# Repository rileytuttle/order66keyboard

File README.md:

# order66keyboard

BUILDING THIS KEYBOARD

checkout this repo
```
git clone git@github.com:rileytuttle/order66keyboard.git
```

HARDWARE - the assumption here is that you have one of my extra pcbs from the small batch fabrication that I used.
otherwise I guess you could have your own made but I doubt that will happen.
note the version of board you have. I forgot to do this with version 1 so if there is no version then you have a v1.0

next step would be to solder the components on
* solder key hotswap sockets
* solder diodes, currently there are two options (either the smd or DO-35 through hole type). make sure to match cathode with silkscreen marking
* choose what kind of battery you want there is an option for a flat type battery using a jst connector or a 18650 battery with a socket.
* choose the battery toggle switch type
* optionally solder sockets for nice!nano
* solder riser socket for nice!view

CASE
* check out the tag corresponding to the version of pcb you have ie `git checkout v1.0` ... use `git tag` to see tags and `git show tagname` to see the annotations. then `git checkout <VERSION_TAG>`
* then open the case.scad file in openscad. there you will be able to choose features corresponding to the optional hardware you have. export the case stl
* export the keygrid stl
* print the files

[Build Photos](./build-photos/)

SOFTWARE
* check out the tag corresponding to the pcb version we have
* build via Docker (needs only Docker/Docker Compose installed, nothing else):
```
docker compose run --rm zmk scripts/build.sh
```
  This uses ZMK's own prebuilt dev image, so the toolchain always matches what's pinned in `config/west.yml`. First run takes a while (clones zmk + Zephyr); later runs are fast.
* or build natively, if you'd rather not use Docker: follow [ZMK's local toolchain setup](https://zmk.dev/docs/development/local-toolchain/setup) to install `west` + the Zephyr SDK, then from the repo root run `./scripts/build.sh`.
* either way, the firmware ends up at `build/zephyr/zmk.uf2` — double-tap reset on the nice!nano to mount it as a USB drive, then copy that file over.

NOTE:
`zmk/` is now a plain, unforked checkout of upstream ZMK managed by `west` (see `config/west.yml`) instead of a custom fork — it's gitignored and recreated by `west update`. The `order66-shield` directory stays a regular git submodule for now.

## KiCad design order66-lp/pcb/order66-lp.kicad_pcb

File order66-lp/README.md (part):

# order66-lp

A ground-up redesign of order66: **60-key 5×12 ortholinear** split by a **54 mm central
band**, **Kailh Choc v1 low profile only**, **per-key RGB backlight**, a **Cirque 40 mm
trackpad** with two dedicated mouse buttons, nice!nano v2, LiPo pouch battery.

Self-contained — nothing here points outside this directory, so it can be lifted into
its own repo with a `git mv`. (The one exception is `tools/port_keymap.py`, which reads
the v1.0 keymap from `../zmk-modules/`; it only needs to run once.)

Current state: **schematic and firmware are done and verified. There is no PCB layout
yet.**

## What changed from v1.0, and why

| | v1.0 | order66-lp |
|---|---|---|
| Keys | 66 (6×12 with only 6 of 12 top-row positions) | 60 (5×12) + 2 mouse buttons |
| Matrix | 6×12, geometric | **6 cols × 11 rows, half-split** |
| Pointing | none | Cirque TM040040 trackpad on I2C |
| Switches | MX hotswap, 19.05 mm | Kailh Choc v1 hotswap, **18.0 × 17.0 mm** |
| Diodes | THT **and** SMD footprint on every key | SMD only, 1N4148WS SOD-323 |
| Display | nice!view on a 1×05 riser | none |
| Battery | 18650 holder **and** LiPo JST | LiPo JST only |
| Backlight | none | 60 × SK6812MINI-E, one chain |
| Passives | **zero** | boost converter, load switch, level shifter |
| ZMK | **patched fork required** | upstream, unmodified |
| Board | 228.6 × 123.0 mm | **280.0 × 95.0 mm** (54 mm band, no back strip) |

Kept deliberately, as redundant build options: both power-switch footprints
(`SW62` EG1206A / `SW63` SSSS811101 — populate one) and both SWD header footprints
(`J2` horizontal / `J3` millmax vertical — normally unpopulated).

### The ZMK fork is gone

v1.0's six top-row `AUX` keys meant the board was not a standard ortholinear, so
ZMK's **shared** `app/dts/layouts/common/ortho_5x12/all1u.dtsi` — the generic layout
used by Contra, Preonic, boardsource5x12 and others — was patched in a fork to grow a
sixth row (commits `90dde5dd` *"back to basics. hacking this common code to get my
keyboard to work. will do it correctly later"* and `eab02c94`). That is the only
reason the root README says you must build locally instead of using
`zmk-config` + GitHub Actions.

All five commits on the fork serve features this board removes: two are that layout
hack, three are nice!view widget rotation. At a true 5×12 with no screen, **upstream
ZMK builds this board with no patches**, and `tools/check_firmware.py` verifies that
upstream's `ortho_5x12` has exactly the 60 keys this shield expects.

It also fixes a latent bug: the fork's patched layout has **71** `key_physical_attrs`
entries against a **72**-entry `position_map` and transform.

Note the distinction: this removes the need for the **fork**, not for a *module*. A
module is just the packaging that lets a `zmk-config` find an out-of-tree shield.

### Relationship to upstream `boardsource5x12`

This board is electrically the same thing as ZMK's own `boardsource5x12` shield:
5×12, `col2row`, nice!nano-compatible. Strip the comments and the **only** difference
between the two overlays is the GPIO lines and one node label. The part that actually
holds complexity -- the physical layout -- is shared: `ortho_5x12/all1u.dtsi` is the
same file Contra, Preonic and boardsource5x12 use.

So why a shield at all? Because `boardsource5x12` hard-codes its own pinout via
`&pro_micro` aliases, which on a nice!nano v2 resolve to:

| | |
|---|---|
| ROW0-4 | `P0.08`, **`P0.06`**, `P0.17`, `P0.20`, `P0.22` |
| COL0-11 | `P0.31`, `P0.29`, `P0.02`, `P1.15`, `P1.13`, `P1.11`, `P0.10`, `P0.09`, `P1.06`, `P1.04`, `P0.11`, `P1.00` |

Using it verbatim would mean routing the PCB to that order. Only 3 of 17 positions
match the assignment here, it takes `P0.06` (the LED data pin) as ROW1, it uses both
NFC pins anyway, and it leaves only `P0.24`/`P1.01`/`P1.02`/`P1.07` spare -- one of
which would become the LED data line. It is a real option, and `nRF52840` SPIM pin
selection is flexible enough to accommodate it, but it trades free routing on a board
whose controller is bottom-mounted and shifted left for someone else's pin order.

The 17 lines of pin definitions in `order66_lp.overlay` are the price of that freedom.
If you would rather pay the routing constraint and drop the shield entirely, re-pin
before layout: the keymap would move to a `zmk-config`, and the backlight devicetree
would have to live inside the `.keymap` file, since a `zmk-config` has no per-shield
board overlay.

## Layout

```
order66-lp/
  pcb/           KiCad 10 project, schematic, exported PDF + BOM
  libraries/     vendored symbol/footprint libraries (see libraries/marbastlib/README.md)
  zmk/           ZMK shield module: boards/shields/order66_lp/
  tools/         schematic generator and verification scripts
```

## Switch and LED footprints

From [`ebastler/marbastlib`](https://github.com/ebastler/marbastlib) (CERN-OHL-P-2.0),
whose current release targets KiCad 10:

- `SW_choc_v1_HS_CPG135001S30_1u` — Choc v1 hotswap. Centre NPTH Ø3.4 at (0,0), pegs
  Ø1.7 at (±5.50, 0), switch pins Ø3.0 at (5, 3.75) and (0, 5.95), socket pads
  reaching x ≈ 9.57.
- `LED_choc_6028R` — *"Add-on for regular choc-footprints with 6028 reverse mount
  LED"*. Four SMD pads at (±2.725, ±0.75) plus a **3.4 × 3.0 mm Edge.Cuts cutout at
  the origin**.

The add-on's cutout lands exactly on the switch footprint's Ø3.4 centre hole: it is
designed to overlay the switch and turn that round hole into the routed slot the LED
drops into. Choc v1's LED window is in the switch **centre**, which is why
shine-through comes up through the middle of the stem.

**Shine-through keycaps** (Choc v1 only, which this design commits to):
[MBK Legend Glow R2](https://keycapsss.com/keyboard-parts/keycaps/181/mbk-legend-glow-r2-black-choc-low-profile-keycap-set)
is the main set — translucent ABS, opaque PU coat, laser-etched legends, described as
adapted to shine uniformly through the Choc LED window.
[MBK Dot Glow](https://www.littlekeyboards.com/products/mbk-glow-keycaps) is the
single-dot version; [icon caps](https://keycapsss.com/Choc-Low-Profile-Keycaps-with-Shine-Through-Icon-Dots/KC10162-1dot)
and translucent [Holo Crystal](https://keycapsss.com/MBK-Choc-Holo-Crystal-Keycap/KC10139-1U)
also exist. Check the kit covers a 5×12 ortho before ordering.

## Matrix: 6 columns × 11 rows, half-split

A 5×12 matrix is 17 pins for 60 positions and is **100 % full** — no room for the mouse
buttons. 6×11 is *the same 17 pins* but 66 positions, so it pays for the buttons and
still leaves 4 spare. It is a strict improvement, not a trade.

- electrical **columns 0–5** = the six physical columns of a half, shared by both halves
- electrical **rows 0–4** = left half, **rows 5–9** = right half
- electrical **row 10** = the two mouse buttons (cols 0–1); cols 2–5 spare

Row nets stay local to one half rather than spanning the board. An 8×8 matrix would have
saved one further pin but cannot be mapped onto two 6-column halves, so ~20 of the 60
keys would land on nets that don't match their physical position.

## Pin assignment — all 21 exposed GPIO used

`COL0–5` and `ROW0–4` keep the pins they had on the 5×12 board; the old `COL6–11` pins
become the right half's `ROW5–10`, so this is a minimal remap rather than a reshuffle.

| | pins |
|---|---|
| COL0–5 | `P0.31` `P1.15` `P1.13` `P0.08` `P0.24` `P1.00` |
| ROW0–4 (left half) | `P0.29` `P0.09` `P0.10` `P1.11` `P0.22` |
| ROW5–10 (right half + buttons) | `P0.11` `P1.02` `P1.07` `P1.04` `P1.06` `P1.01` |
| LED data | `P0.06` (SPIM3 MOSI) |
| trackpad I2C | `P0.17` SDA / `P0.20` SCL — the nice!nano's own `&i2c0` pins |
| trackpad data-ready | `P0.02` |

17 matrix + 1 LED + 2 I2C + 1 IRQ = **21 of 21**. No spare GPIO, but 4 spare matrix
positions.

The I2C assignment is a lucky one: the nice!nano already pins `&i2c0` to TWIM_SDA on
`P0.17` and TWIM_SCL on `P0.20`, so the firmware needs no pinctrl override at all.

## Trackpad

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
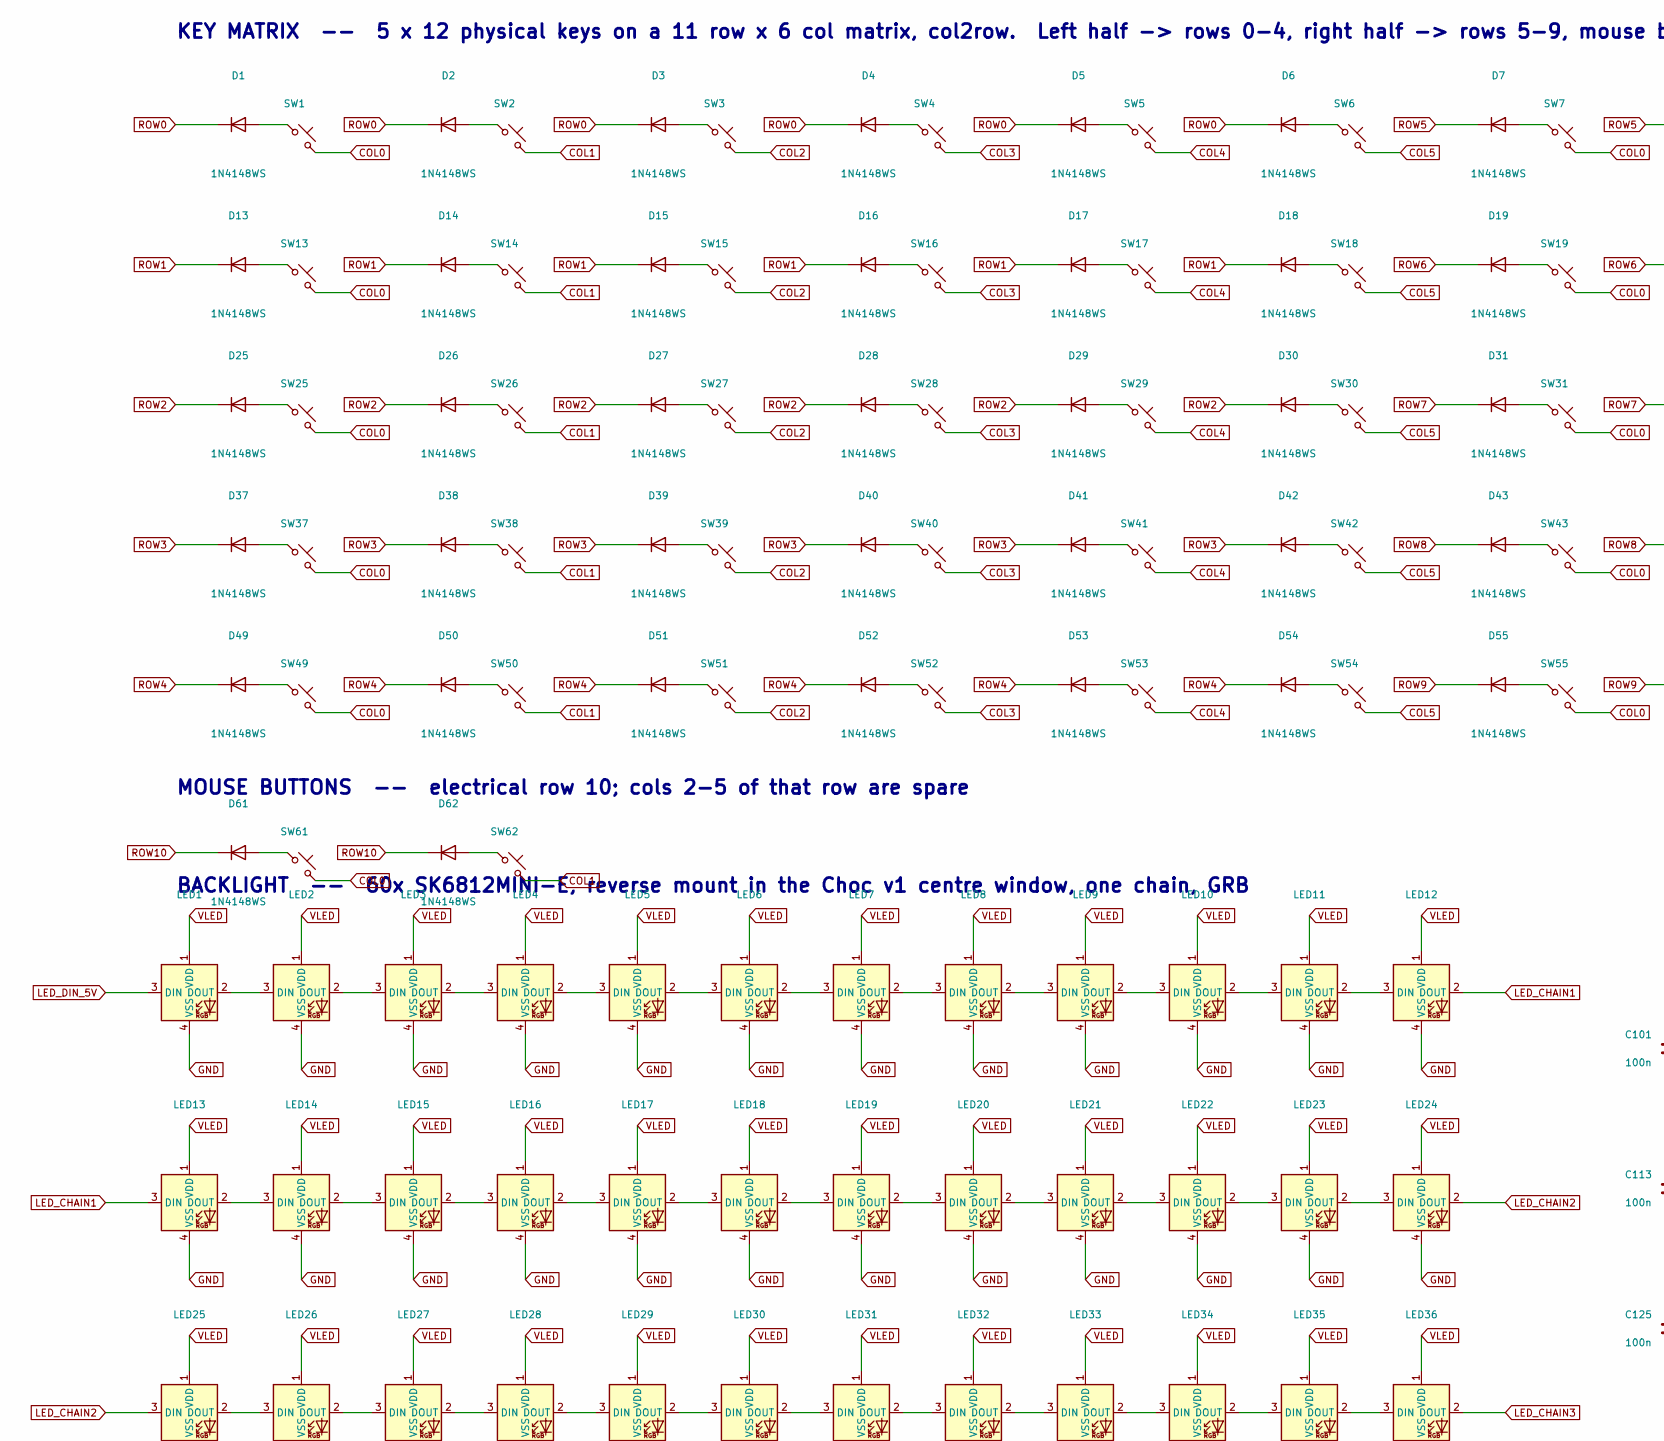
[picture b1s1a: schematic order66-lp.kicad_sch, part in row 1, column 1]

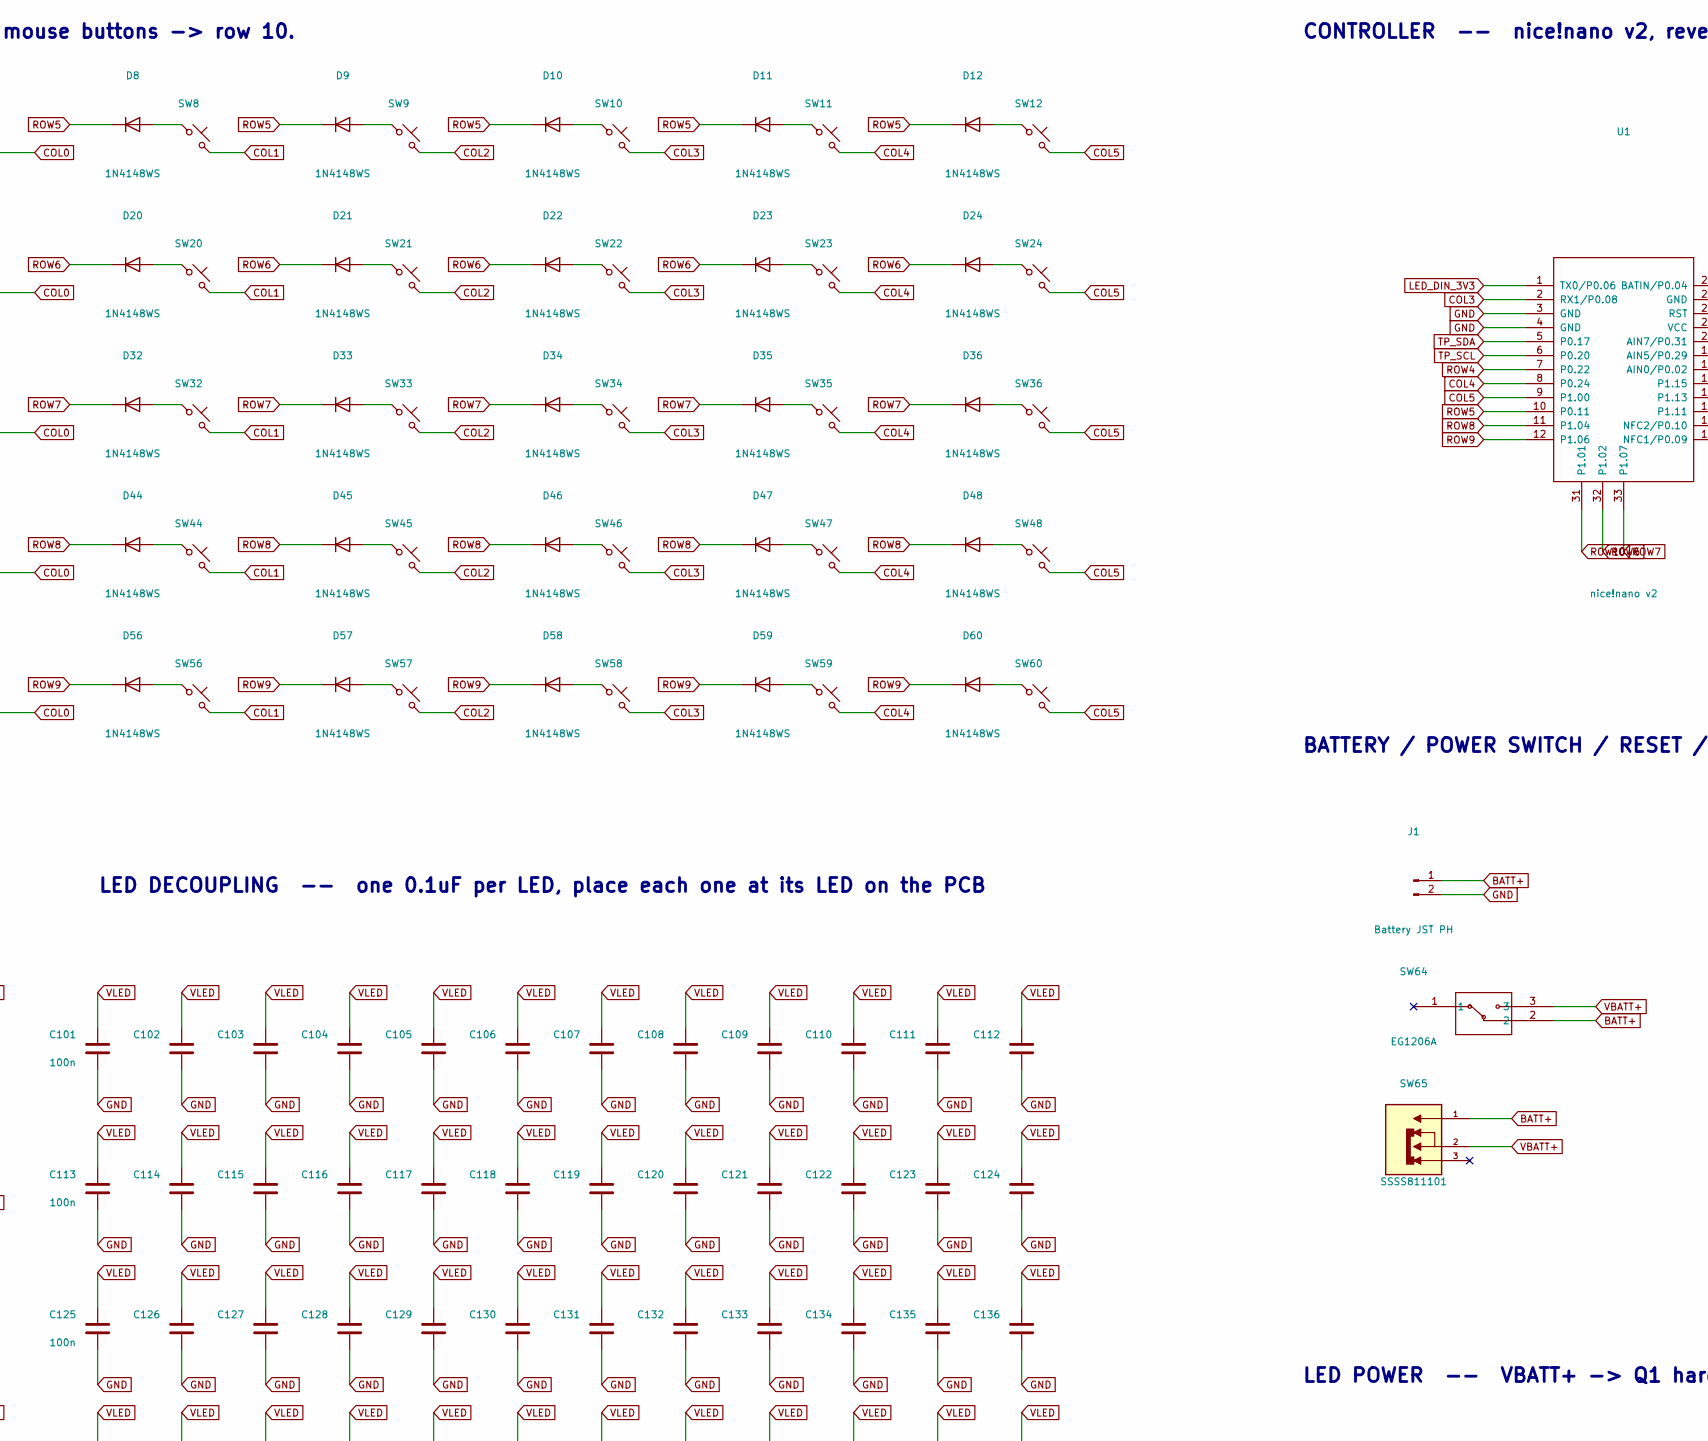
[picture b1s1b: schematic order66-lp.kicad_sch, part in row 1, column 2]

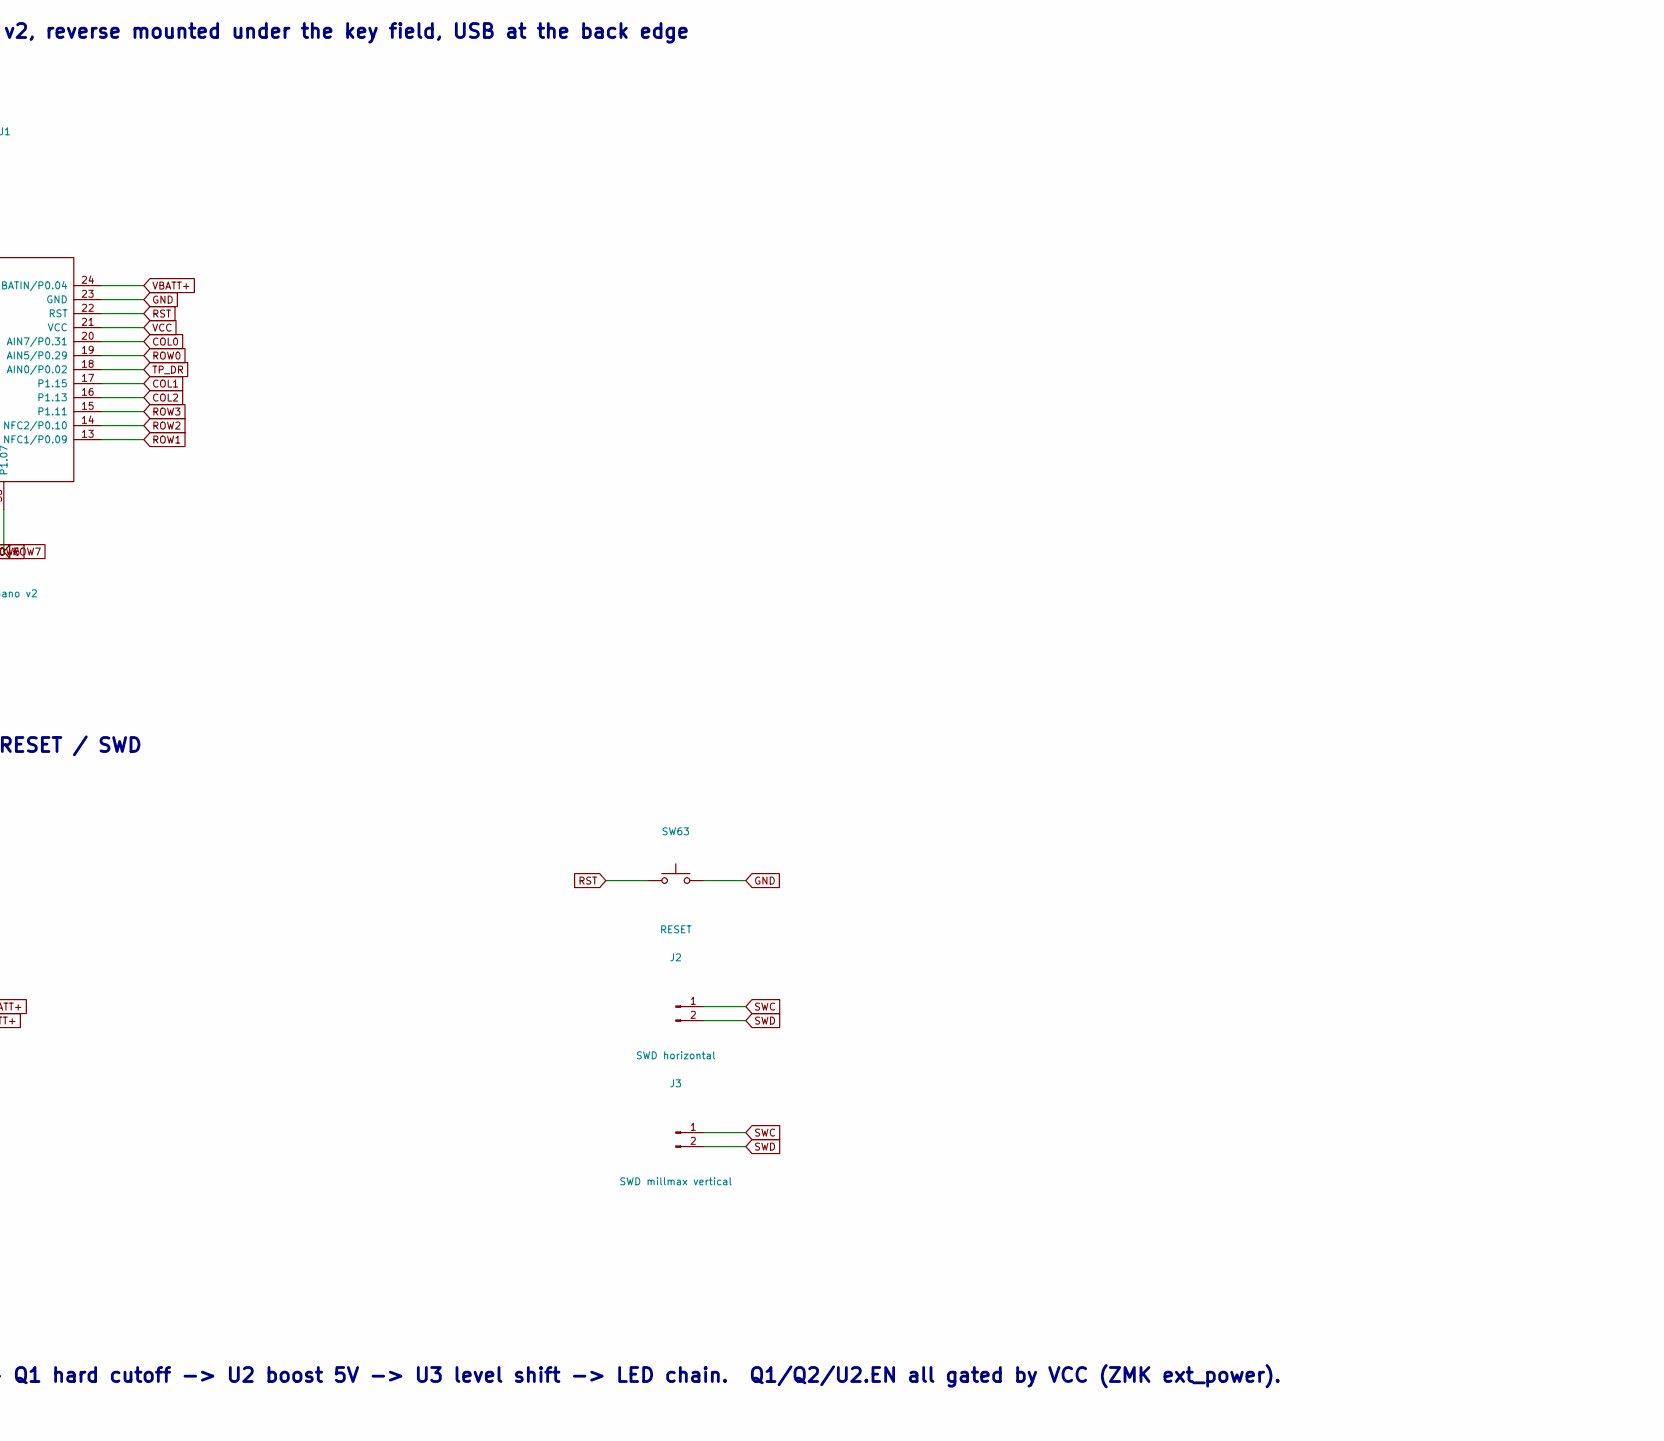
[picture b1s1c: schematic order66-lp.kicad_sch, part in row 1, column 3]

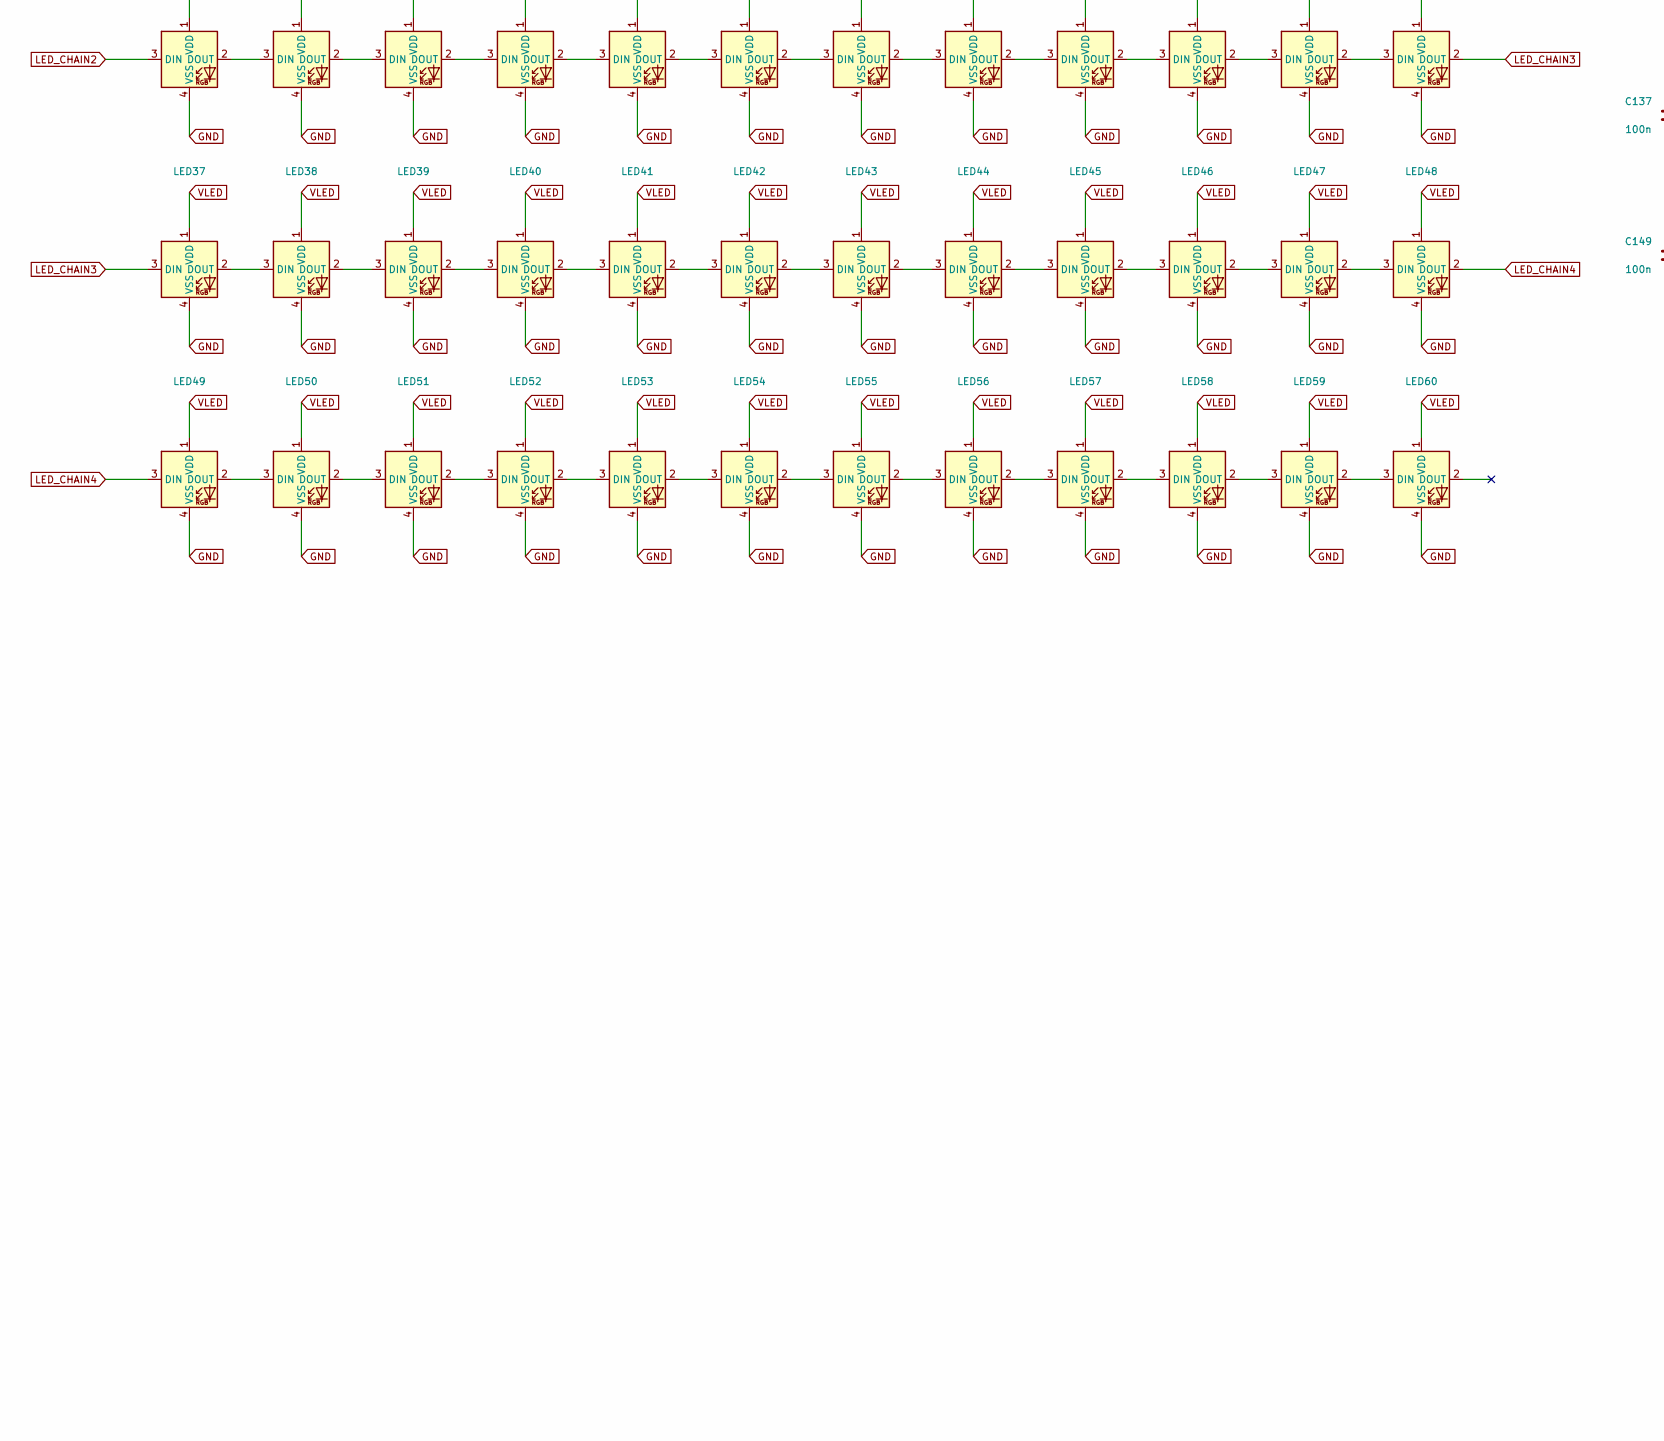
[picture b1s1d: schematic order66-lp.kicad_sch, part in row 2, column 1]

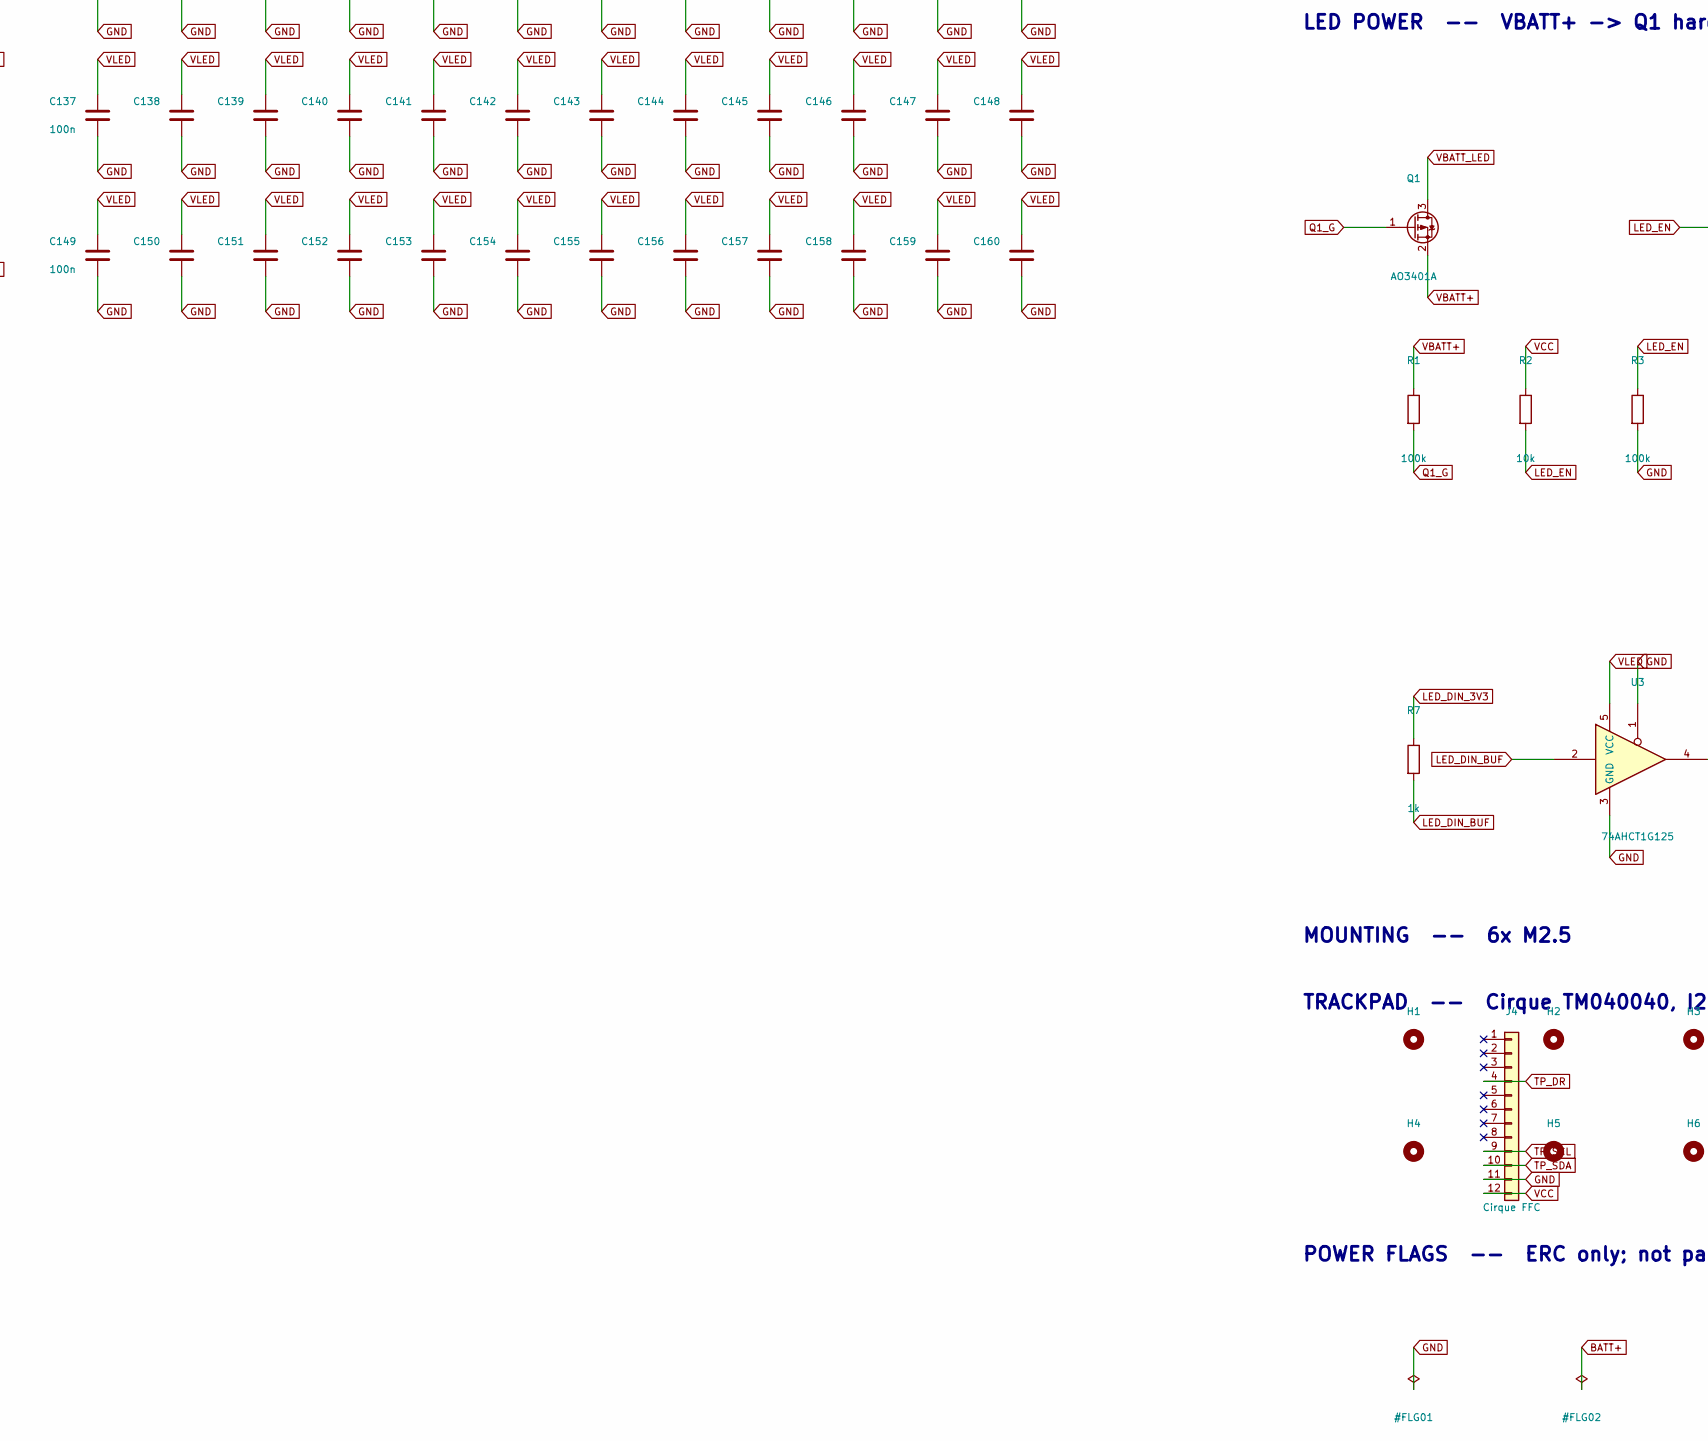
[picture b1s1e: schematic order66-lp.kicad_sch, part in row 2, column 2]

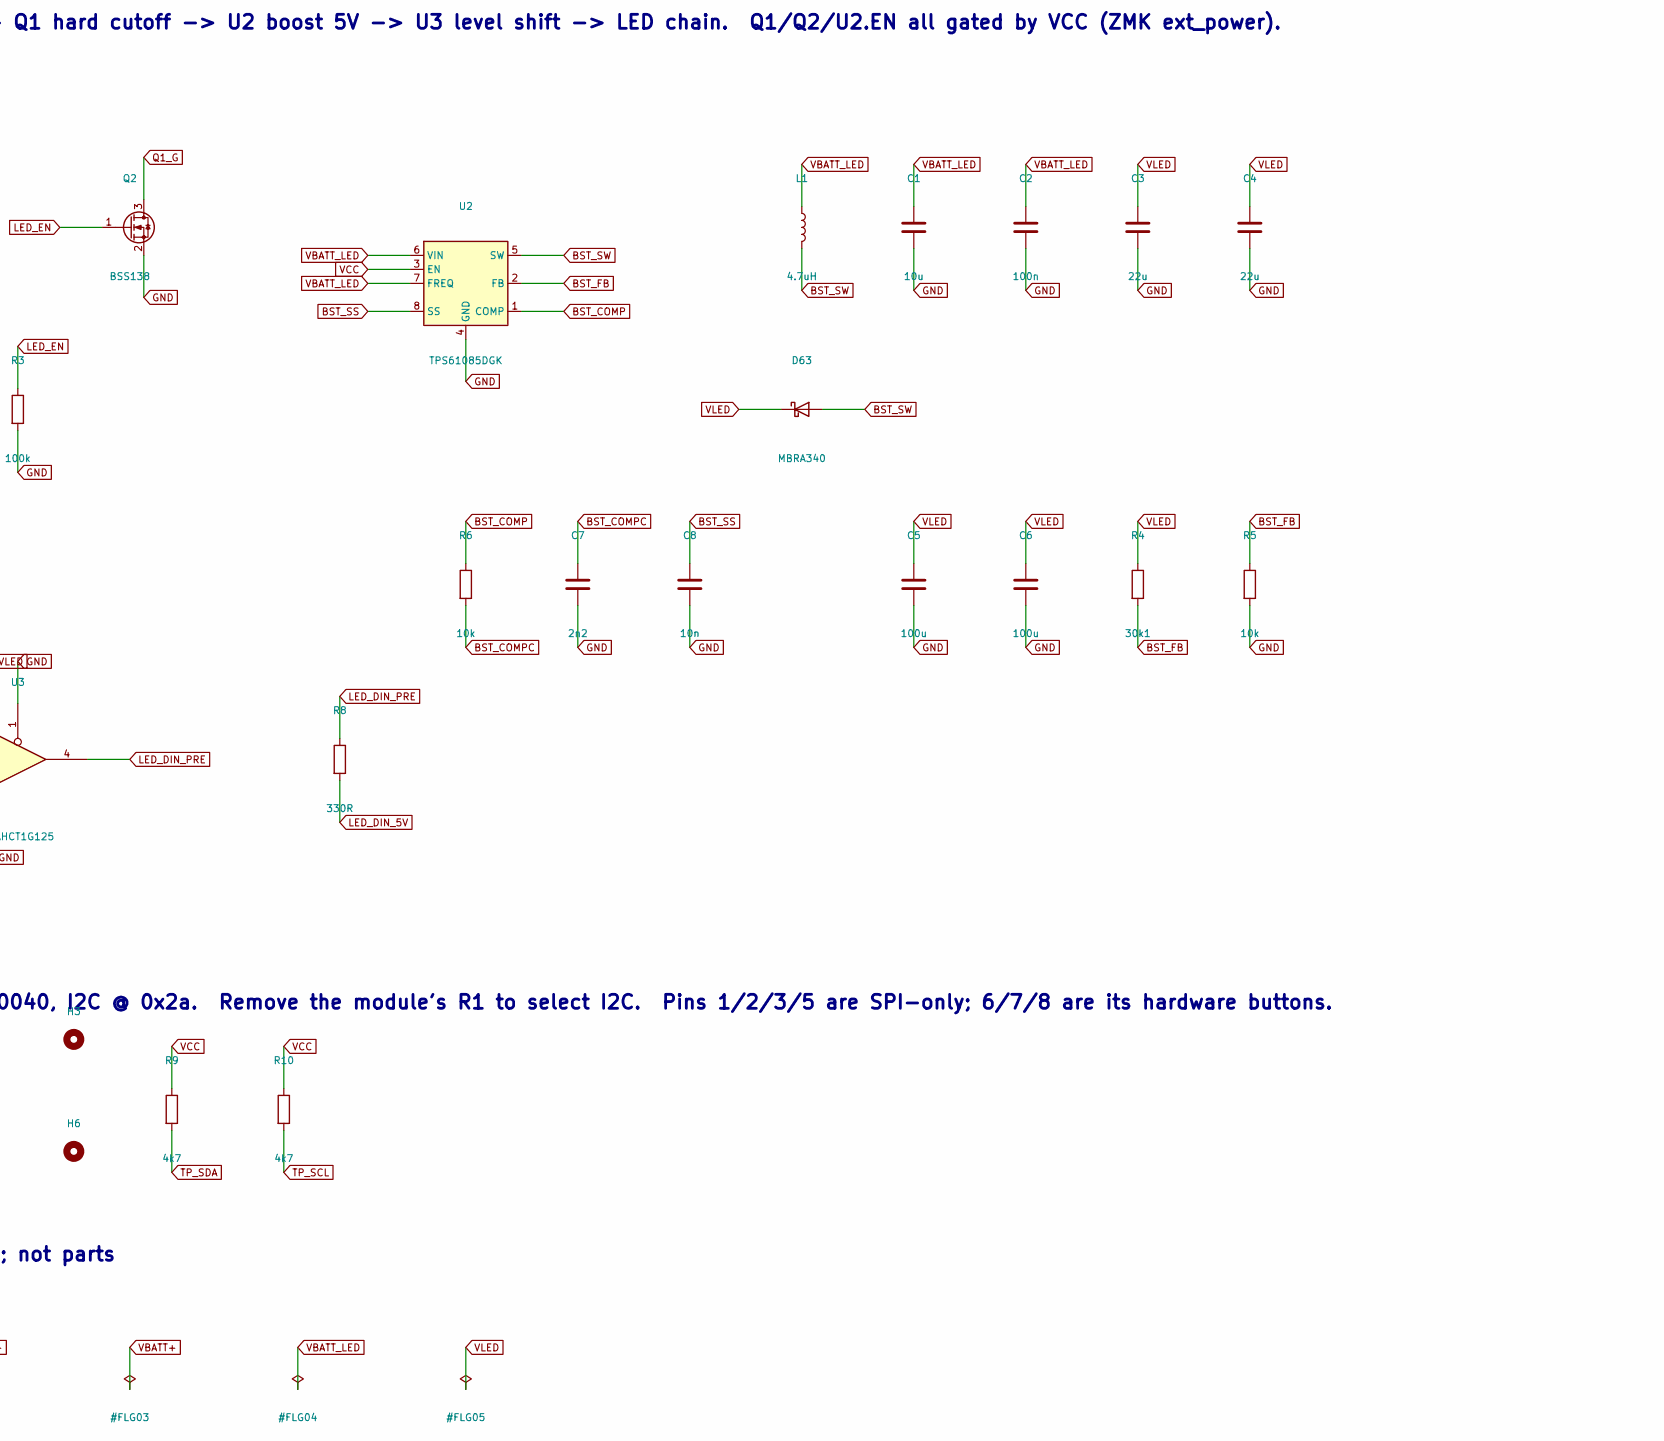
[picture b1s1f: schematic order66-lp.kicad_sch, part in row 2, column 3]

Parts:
C1: 10u; C_0805_2012Metric
C2, C101, C102, C103, C104, C105, C106, C107, C108, C109, C110, C111, C112, C113, C114, C115, C116, C117, C118, C119, C120, C121, C122, C123, C124, C125, C126, C127, C128, C129, C130, C131, C132, C133, C134, C135, C136, C137, C138, C139, C140, C141, C142, C143, C144, C145, C146, C147, C148, C149, C150, C151, C152, C153, C154, C155, C156, C157, C158, C159, C160: 100n; C_0402_1005Metric
C3, C4: 22u; C_0805_2012Metric
C5, C6: 100u; C_1210_3225Metric
C7: 2n2; C_0402_1005Metric
C8: 10n; C_0402_1005Metric
D1, D2, D3, D4, D5, D6, D7, D8, D9, D10, D11, D12, D13, D14, D15, D16, D17, D18, D19, D20, D21, D22, D23, D24, D25, D26, D27, D28, D29, D30, D31, D32, D33, D34, D35, D36, D37, D38, D39, D40, D41, D42, D43, D44, D45, D46, D47, D48, D49, D50, D51, D52, D53, D54, D55, D56, D57, D58, D59, D60, D61, D62: 1N4148WS; D_SOD-323
D63: MBRA340; D_SMA
H1, H2, H3, H4, H5, H6: MountingHole; MountingHole_2.7mm_M2.5
J1: Battery JST PH; JST_PH_B2B-PH-K_1x02_P2.00mm_Vertical
J2: SWD horizontal; PinHeader_1x02_P2.54mm_Horizontal
J3: SWD millmax vertical; PinHeader_1x02_P2.54mm_Vertical
J4: Cirque FFC; CON_FH33J-12S-0.5SH
L1: 4.7uH; L_Taiyo-Yuden_NR-30xx
LED1, LED2, LED3, LED4, LED5, LED6, LED7, LED8, LED9, LED10, LED11, LED12, LED13, LED14, LED15, LED16, LED17, LED18, LED19, LED20, LED21, LED22, LED23, LED24, LED25, LED26, LED27, LED28, LED29, LED30, LED31, LED32, LED33, LED34, LED35, LED36, LED37, LED38, LED39, LED40, LED41, LED42, LED43, LED44, LED45, LED46, LED47, LED48, LED49, LED50, LED51, LED52, LED53, LED54, LED55, LED56, LED57, LED58, LED59, LED60: SK6812MINI-E; LED_choc_6028R
Q1: AO3401A; SOT-23
Q2: BSS138; SOT-23
R1, R3: 100k; R_0402_1005Metric
R2, R5, R6: 10k; R_0402_1005Metric
R4: 30k1; R_0402_1005Metric
R7: 1k; R_0402_1005Metric
R8: 330R; R_0402_1005Metric
R9, R10: 4k7; R_0402_1005Metric
SW1, SW2, SW3, SW4, SW5, SW6, SW7, SW8, SW9, SW10, SW11, SW12, SW13, SW14, SW15, SW16, SW17, SW18, SW19, SW20, SW21, SW22, SW23, SW24, SW25, SW26, SW27, SW28, SW29, SW30, SW31, SW32, SW33, SW34, SW35, SW36, SW37, SW38, SW39, SW40, SW41, SW42, SW43, SW44, SW45, SW46, SW47, SW48, SW49, SW50, SW51, SW52, SW53, SW54, SW55, SW56, SW57, SW58, SW59, SW60: CHOC_V1_HS; SW_choc_v1_HS_CPG135001S30_1u
SW61, SW62: MOUSE_BTN; SW_choc_v1_HS_CPG135001S30_1u
SW63: RESET; SW_TH_Tactile_Omron_B3F-100x
SW64: EG1206A; EG1206A_EWI
SW65: SSSS811101; SW_SSSS811101
U1: nice!nano v2; nice_nano_Hdr_TH1-12_SMD13-33
U2: TPS61085DGK; VSSOP-8_3x3mm_P0.65mm
U3: 74AHCT1G125; SOT-353_SC-70-5

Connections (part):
BATT+: J1.1, SW64.2, SW65.1
BST_COMP: R6.1, U2.1 (COMP)
BST_COMPC: C7.1, R6.2
BST_FB: R4.2, R5.1, U2.2 (FB)
BST_SS: C8.1, U2.8 (SS)
BST_SW: D63.2 (A), L1.2, U2.5 (SW)
COL0: SW1.2, SW7.2, SW13.2, SW19.2, SW25.2, SW31.2, SW37.2, SW43.2, SW49.2, SW55.2, SW61.2, U1.20 (AIN7/P0.31)
COL1: SW2.2, SW8.2, SW14.2, SW20.2, SW26.2, SW32.2, SW38.2, SW44.2, SW50.2, SW56.2, SW62.2, U1.17 (P1.15)
COL2: SW3.2, SW9.2, SW15.2, SW21.2, SW27.2, SW33.2, SW39.2, SW45.2, SW51.2, SW57.2, U1.16 (P1.13)
COL3: SW4.2, SW10.2, SW16.2, SW22.2, SW28.2, SW34.2, SW40.2, SW46.2, SW52.2, SW58.2, U1.2 (RX1/P0.08)
COL4: SW5.2, SW11.2, SW17.2, SW23.2, SW29.2, SW35.2, SW41.2, SW47.2, SW53.2, SW59.2, U1.8 (P0.24)
COL5: SW6.2, SW12.2, SW18.2, SW24.2, SW30.2, SW36.2, SW42.2, SW48.2, SW54.2, SW60.2, U1.9 (P1.00)
GND: C1.2, C2.2, C3.2, C4.2, C5.2, C6.2, C7.2, C8.2, C101.2, C102.2, C103.2, C104.2, C105.2, C106.2, C107.2, C108.2, C109.2, C110.2, C111.2, C112.2, C113.2, C114.2, C115.2, C116.2, C117.2, C118.2, C119.2, C120.2, C121.2, C122.2, C123.2, C124.2, C125.2, C126.2, C127.2, C128.2, C129.2, C130.2, C131.2, C132.2, C133.2, C134.2, C135.2, C136.2, C137.2, C138.2, C139.2, C140.2, C141.2, C142.2, C143.2, C144.2, C145.2, C146.2, C147.2, C148.2, C149.2, C150.2, C151.2, C152.2, C153.2, C154.2, C155.2, C156.2, C157.2, C158.2, C159.2, C160.2, J1.2, J4.11, LED1.4 (VSS), LED2.4 (VSS), LED3.4 (VSS), LED4.4 (VSS), LED5.4 (VSS), LED6.4 (VSS), LED7.4 (VSS), LED8.4 (VSS), LED9.4 (VSS), LED10.4 (VSS), LED11.4 (VSS), LED12.4 (VSS)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
LED_CHAIN1: LED12.2 (DOUT), LED13.3 (DIN)
LED_CHAIN2: LED24.2 (DOUT), LED25.3 (DIN)
LED_CHAIN3: LED36.2 (DOUT), LED37.3 (DIN)
LED_CHAIN4: LED48.2 (DOUT), LED49.3 (DIN)
LED_DIN_3V3: R7.1, U1.1 (TX0/P0.06)
LED_DIN_5V: LED1.3 (DIN), R8.2
LED_DIN_BUF: R7.2, U3.2
LED_DIN_PRE: R8.1, U3.4
LED_EN: Q2.1 (G), R2.2, R3.1
unnamed: D1.2 (A), SW1.1
unnamed: D2.2 (A), SW2.1
unnamed: D3.2 (A), SW3.1
unnamed: D4.2 (A), SW4.1
unnamed: D5.2 (A), SW5.1
unnamed: D6.2 (A), SW6.1
unnamed: D7.2 (A), SW7.1
unnamed: D8.2 (A), SW8.1
unnamed: D9.2 (A), SW9.1
unnamed: D10.2 (A), SW10.1
unnamed: D11.2 (A), SW11.1
unnamed: D12.2 (A), SW12.1
unnamed: D13.2 (A), SW13.1
unnamed: D14.2 (A), SW14.1
unnamed: D15.2 (A), SW15.1
unnamed: D16.2 (A), SW16.1
unnamed: D17.2 (A), SW17.1
unnamed: D18.2 (A), SW18.1
unnamed: D19.2 (A), SW19.1
unnamed: D20.2 (A), SW20.1
unnamed: D21.2 (A), SW21.1
unnamed: D22.2 (A), SW22.1
unnamed: D23.2 (A), SW23.1
unnamed: D24.2 (A), SW24.1
unnamed: D25.2 (A), SW25.1
unnamed: D26.2 (A), SW26.1
unnamed: D27.2 (A), SW27.1
unnamed: D28.2 (A), SW28.1
unnamed: D29.2 (A), SW29.1
unnamed: D30.2 (A), SW30.1
unnamed: D31.2 (A), SW31.1
unnamed: D32.2 (A), SW32.1
unnamed: D33.2 (A), SW33.1
unnamed: D34.2 (A), SW34.1
unnamed: D35.2 (A), SW35.1
unnamed: D36.2 (A), SW36.1
unnamed: D37.2 (A), SW37.1
unnamed: D38.2 (A), SW38.1
unnamed: D39.2 (A), SW39.1
unnamed: D40.2 (A), SW40.1
unnamed: D41.2 (A), SW41.1
unnamed: D42.2 (A), SW42.1
unnamed: D43.2 (A), SW43.1
unnamed: D44.2 (A), SW44.1
unnamed: D45.2 (A), SW45.1
unnamed: D46.2 (A), SW46.1
unnamed: D47.2 (A), SW47.1
unnamed: D48.2 (A), SW48.1
unnamed: D49.2 (A), SW49.1
unnamed: D50.2 (A), SW50.1
unnamed: D51.2 (A), SW51.1
unnamed: D52.2 (A), SW52.1
unnamed: D53.2 (A), SW53.1
unnamed: D54.2 (A), SW54.1
unnamed: D55.2 (A), SW55.1
unnamed: D56.2 (A), SW56.1
unnamed: D57.2 (A), SW57.1
unnamed: D58.2 (A), SW58.1
unnamed: D59.2 (A), SW59.1
unnamed: D60.2 (A), SW60.1
unnamed: D61.2 (A), SW61.1
unnamed: D62.2 (A), SW62.1
unnamed: LED1.2 (DOUT), LED2.3 (DIN)
unnamed: LED2.2 (DOUT), LED3.3 (DIN)
unnamed: LED3.2 (DOUT), LED4.3 (DIN)
unnamed: LED4.2 (DOUT), LED5.3 (DIN)
unnamed: LED5.2 (DOUT), LED6.3 (DIN)
unnamed: LED6.2 (DOUT), LED7.3 (DIN)
unnamed: LED7.2 (DOUT), LED8.3 (DIN)
unnamed: LED8.2 (DOUT), LED9.3 (DIN)
unnamed: LED9.2 (DOUT), LED10.3 (DIN)
unnamed: LED10.2 (DOUT), LED11.3 (DIN)
unnamed: LED11.2 (DOUT), LED12.3 (DIN)
unnamed: LED13.2 (DOUT), LED14.3 (DIN)
unnamed: LED14.2 (DOUT), LED15.3 (DIN)
unnamed: LED15.2 (DOUT), LED16.3 (DIN)
unnamed: LED16.2 (DOUT), LED17.3 (DIN)
unnamed: LED17.2 (DOUT), LED18.3 (DIN)
unnamed: LED18.2 (DOUT), LED19.3 (DIN)
unnamed: LED19.2 (DOUT), LED20.3 (DIN)
unnamed: LED20.2 (DOUT), LED21.3 (DIN)
unnamed: LED21.2 (DOUT), LED22.3 (DIN)
unnamed: LED22.2 (DOUT), LED23.3 (DIN)
unnamed: LED23.2 (DOUT), LED24.3 (DIN)
unnamed: LED25.2 (DOUT), LED26.3 (DIN)
unnamed: LED26.2 (DOUT), LED27.3 (DIN)
unnamed: LED27.2 (DOUT), LED28.3 (DIN)
unnamed: LED28.2 (DOUT), LED29.3 (DIN)
unnamed: LED29.2 (DOUT), LED30.3 (DIN)
unnamed: LED30.2 (DOUT), LED31.3 (DIN)
unnamed: LED31.2 (DOUT), LED32.3 (DIN)
unnamed: LED32.2 (DOUT), LED33.3 (DIN)
unnamed: LED33.2 (DOUT), LED34.3 (DIN)
unnamed: LED34.2 (DOUT), LED35.3 (DIN)
unnamed: LED35.2 (DOUT), LED36.3 (DIN)
unnamed: LED37.2 (DOUT), LED38.3 (DIN)
unnamed: LED38.2 (DOUT), LED39.3 (DIN)
unnamed: LED39.2 (DOUT), LED40.3 (DIN)
unnamed: LED40.2 (DOUT), LED41.3 (DIN)
unnamed: LED41.2 (DOUT), LED42.3 (DIN)
unnamed: LED42.2 (DOUT), LED43.3 (DIN)
unnamed: LED43.2 (DOUT), LED44.3 (DIN)
unnamed: LED44.2 (DOUT), LED45.3 (DIN)
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
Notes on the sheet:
KEY MATRIX -- 5 x 12 physical keys on a 11 row x 6 col matrix, col2row. Left half -> rows 0-4, right half -> rows 5-9, mouse buttons -> row 10.
MOUSE BUTTONS -- electrical row 10; cols 2-5 of that row are spare
TRACKPAD -- Cirque TM040040, I2C @ 0x2a. Remove the module's R1 to select I2C. Pins 1/2/3/5 are SPI-only; 6/7/8 are its hardware buttons.
BACKLIGHT -- 60x SK6812MINI-E, reverse mount in the Choc v1 centre window, one chain, GRB
LED DECOUPLING -- one 0.1uF per LED, place each one at its LED on the PCB
CONTROLLER -- nice!nano v2, reverse mounted under the key field, USB at the back edge
BATTERY / POWER SWITCH / RESET / SWD
LED POWER -- VBATT+ -> Q1 hard cutoff -> U2 boost 5V -> U3 level shift -> LED chain. Q1/Q2/U2.EN all gated by VCC (ZMK ext_power).
MOUNTING -- 6x M2.5
POWER FLAGS -- ERC only; not parts

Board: 2 copper layers, 282 parts (276 on the bottom side), 161 nets, no tracks yet.

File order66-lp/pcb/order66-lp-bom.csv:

"Reference","Value","Footprint"
"C1","10u","Capacitor_SMD:C_0805_2012Metric"
"C2,C101-C160","100n","Capacitor_SMD:C_0402_1005Metric"
"C3,C4","22u","Capacitor_SMD:C_0805_2012Metric"
"C5,C6","100u","Capacitor_SMD:C_1210_3225Metric"
"C7","2n2","Capacitor_SMD:C_0402_1005Metric"
"C8","10n","Capacitor_SMD:C_0402_1005Metric"
"D1-D62","1N4148WS","Diode_SMD:D_SOD-323"
"D63","MBRA340","Diode_SMD:D_SMA"
"H1-H6","MountingHole","MountingHole:MountingHole_2.7mm_M2.5"
"J1","Battery JST PH","Connector_JST:JST_PH_B2B-PH-K_1x02_P2.00mm_Vertical"
"J2","SWD horizontal","Connector_PinHeader_2.54mm:PinHeader_1x02_P2.54mm_Horizontal"
"J3","SWD millmax vertical","Connector_PinHeader_2.54mm:PinHeader_1x02_P2.54mm_Vertical"
"J4","Cirque FFC","marbastlib-various:CON_FH33J-12S-0.5SH"
"L1","4.7uH","Inductor_SMD:L_Taiyo-Yuden_NR-30xx"
"LED1-LED60","SK6812MINI-E","marbastlib-choc:LED_choc_6028R"
"Q1","AO3401A","Package_TO_SOT_SMD:SOT-23"
"Q2","BSS138","Package_TO_SOT_SMD:SOT-23"
"R1,R3","100k","Resistor_SMD:R_0402_1005Metric"
"R2,R5,R6","10k","Resistor_SMD:R_0402_1005Metric"
"R4","30k1","Resistor_SMD:R_0402_1005Metric"
"R7","1k","Resistor_SMD:R_0402_1005Metric"
"R8","330R","Resistor_SMD:R_0402_1005Metric"
"R9,R10","4k7","Resistor_SMD:R_0402_1005Metric"
"SW1-SW60","CHOC_V1_HS","marbastlib-choc:SW_choc_v1_HS_CPG135001S30_1u"
"SW61,SW62","MOUSE_BTN","marbastlib-choc:SW_choc_v1_HS_CPG135001S30_1u"
"SW63","RESET","Button_Switch_THT:SW_TH_Tactile_Omron_B3F-100x"
"SW64","EG1206A","EG1206A:EG1206A_EWI"
"SW65","SSSS811101","SSSS811101:SW_SSSS811101"
"U1","nice!nano v2","order66lp:nice_nano_Hdr_TH1-12_SMD13-33"
"U2","TPS61085DGK","Package_SO:VSSOP-8_3x3mm_P0.65mm"
"U3","74AHCT1G125","Package_TO_SOT_SMD:SOT-353_SC-70-5"
